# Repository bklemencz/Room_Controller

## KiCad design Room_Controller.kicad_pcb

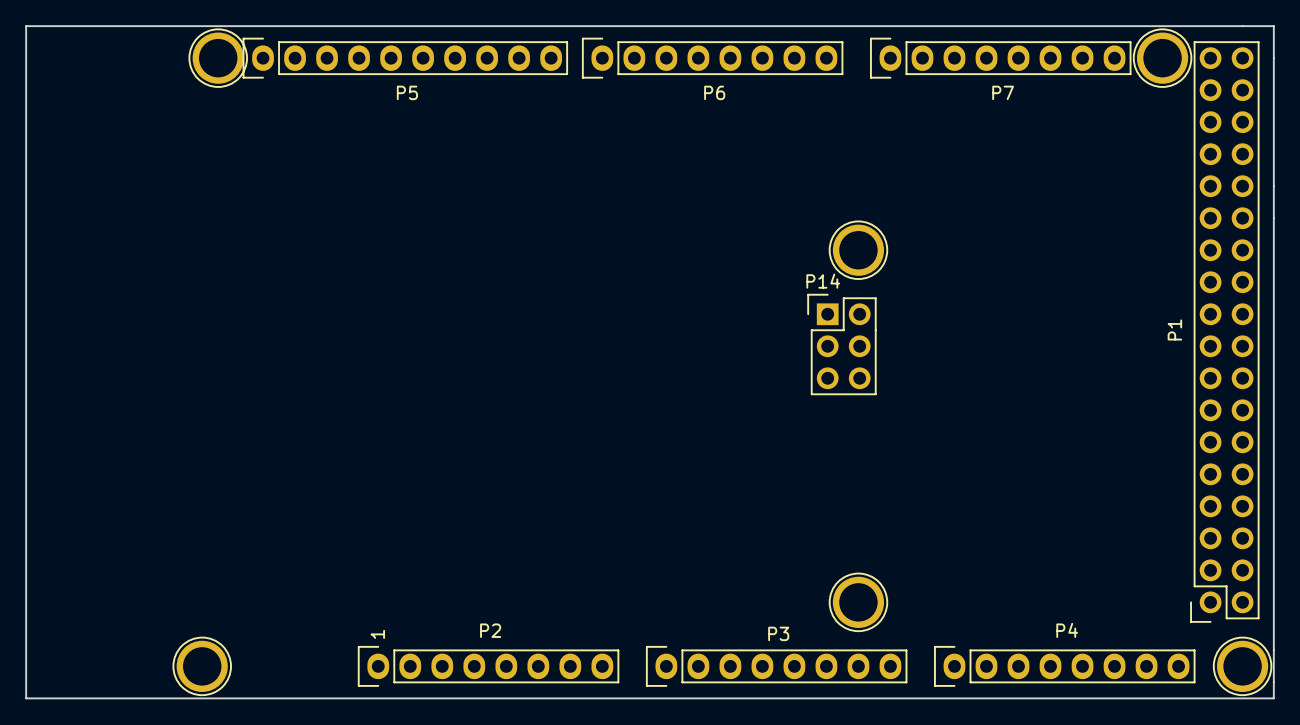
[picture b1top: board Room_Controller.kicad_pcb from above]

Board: 2 copper layers, 99.0 x 53.3 mm, 14 parts (0 on the bottom side), 3 nets, no tracks yet.

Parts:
P1: Digital; Socket_Strip_Arduino_2x18
P2: Power; Socket_Strip_Arduino_1x08
P3, P4: Analog; Socket_Strip_Arduino_1x08
P5: PWM; Socket_Strip_Arduino_1x10
P6: PWM; Socket_Strip_Arduino_1x08
P7: Communication; Socket_Strip_Arduino_1x08
P8, P9, P10, P11, P12, P13: CONN_1; Arduino_1pin
P14: ICSP; Pin_Header_Straight_2x03

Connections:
+5V: P1.35, P1.36, P2.5, P14.2
/Reset: P2.3, P14.5
GND: P1.1, P1.2, P2.6, P2.7, P5.4, P14.6

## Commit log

2016-03-28 :octocat: Added .gitattributes & .gitignore files
2016-03-28 Initial
